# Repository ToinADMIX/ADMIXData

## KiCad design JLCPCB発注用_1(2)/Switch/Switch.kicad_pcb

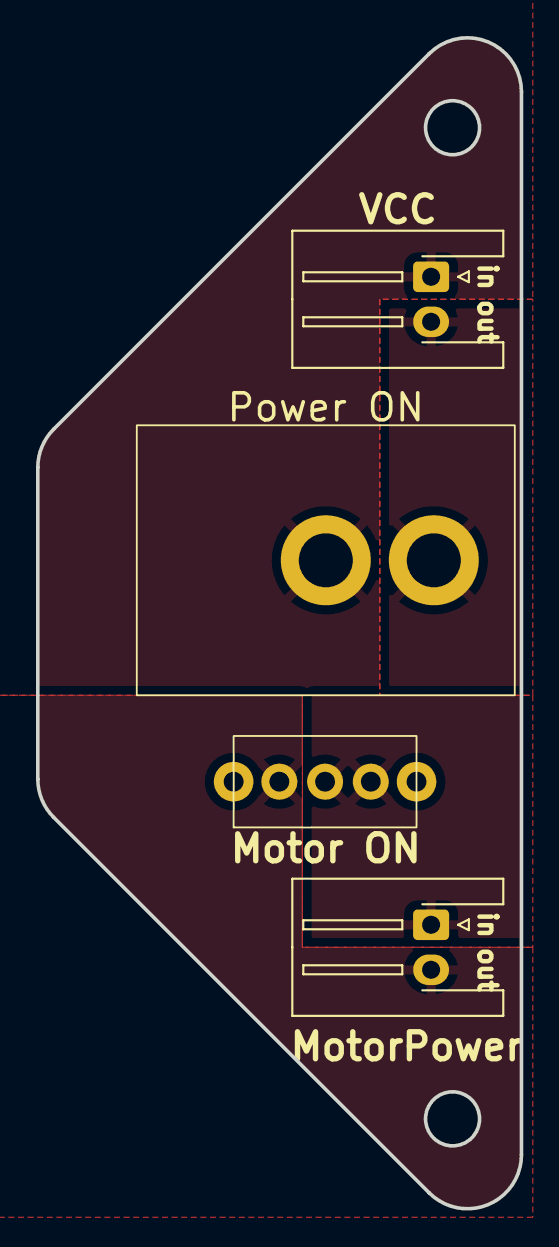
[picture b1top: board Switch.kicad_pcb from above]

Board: 2 copper layers, 26.9 x 65.1 mm, 4 parts (0 on the bottom side), 4 nets, no tracks yet.

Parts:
MotorPower: MotorPower; JST_XH_S2B-XH-A-1_1x02_P2.50mm_Horizontal
Power ON: SW_DPST_x2; DS-850K-S-WD
SW2: SW_DPDT_x2; ToggleSwitch
VCC: VCC; JST_XH_S2B-XH-A-1_1x02_P2.50mm_Horizontal

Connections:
MotorPowerfromPS1: MotorPower.1, SW2.2 (B), SW2.3 (C)
MotorPowertoPS1: MotorPower.2, SW2.1 (A)
VCCfromPS: Power ON.1 (A), VCC.1
VCCtoPS: Power ON.2 (B), VCC.2

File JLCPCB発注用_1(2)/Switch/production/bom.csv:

Designator,Footprint,Quantity,Value,LCSC Part #
MotorPower,JST_XH_S2B-XH-A-1_1x02_P2.50mm_Horizontal,1,MotorPower,
Power ON,DS-850K-S-WD,1,SW_DPST_x2,
SW2,ToggleSwitch,1,SW_DPDT_x2,
VCC,JST_XH_S2B-XH-A-1_1x02_P2.50mm_Horizontal,1,VCC,

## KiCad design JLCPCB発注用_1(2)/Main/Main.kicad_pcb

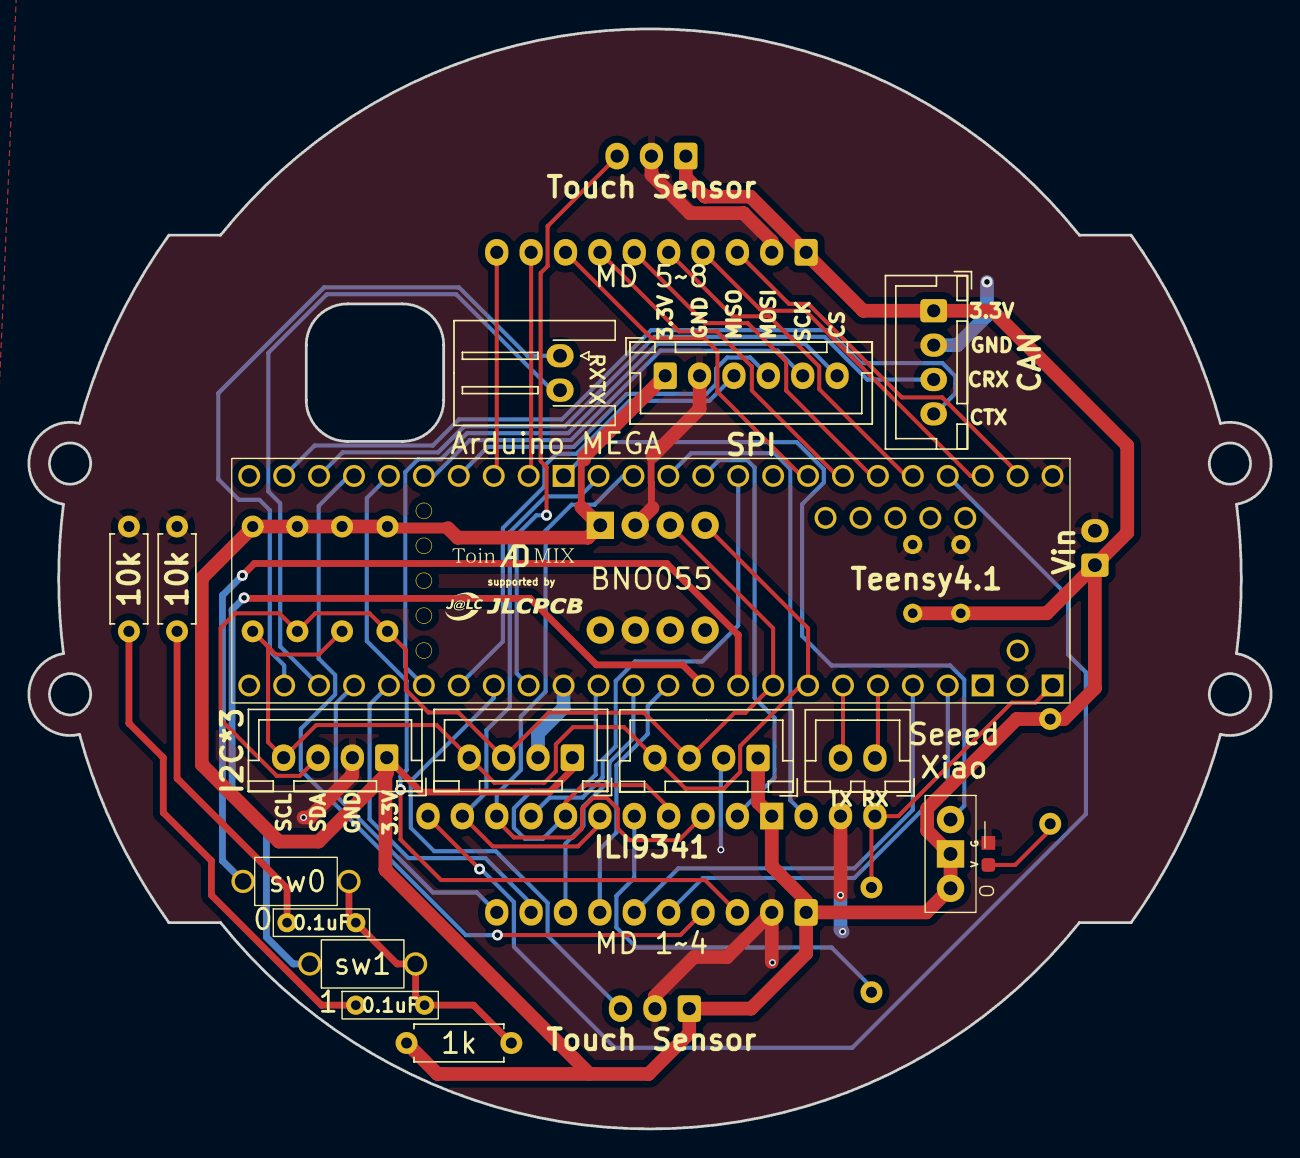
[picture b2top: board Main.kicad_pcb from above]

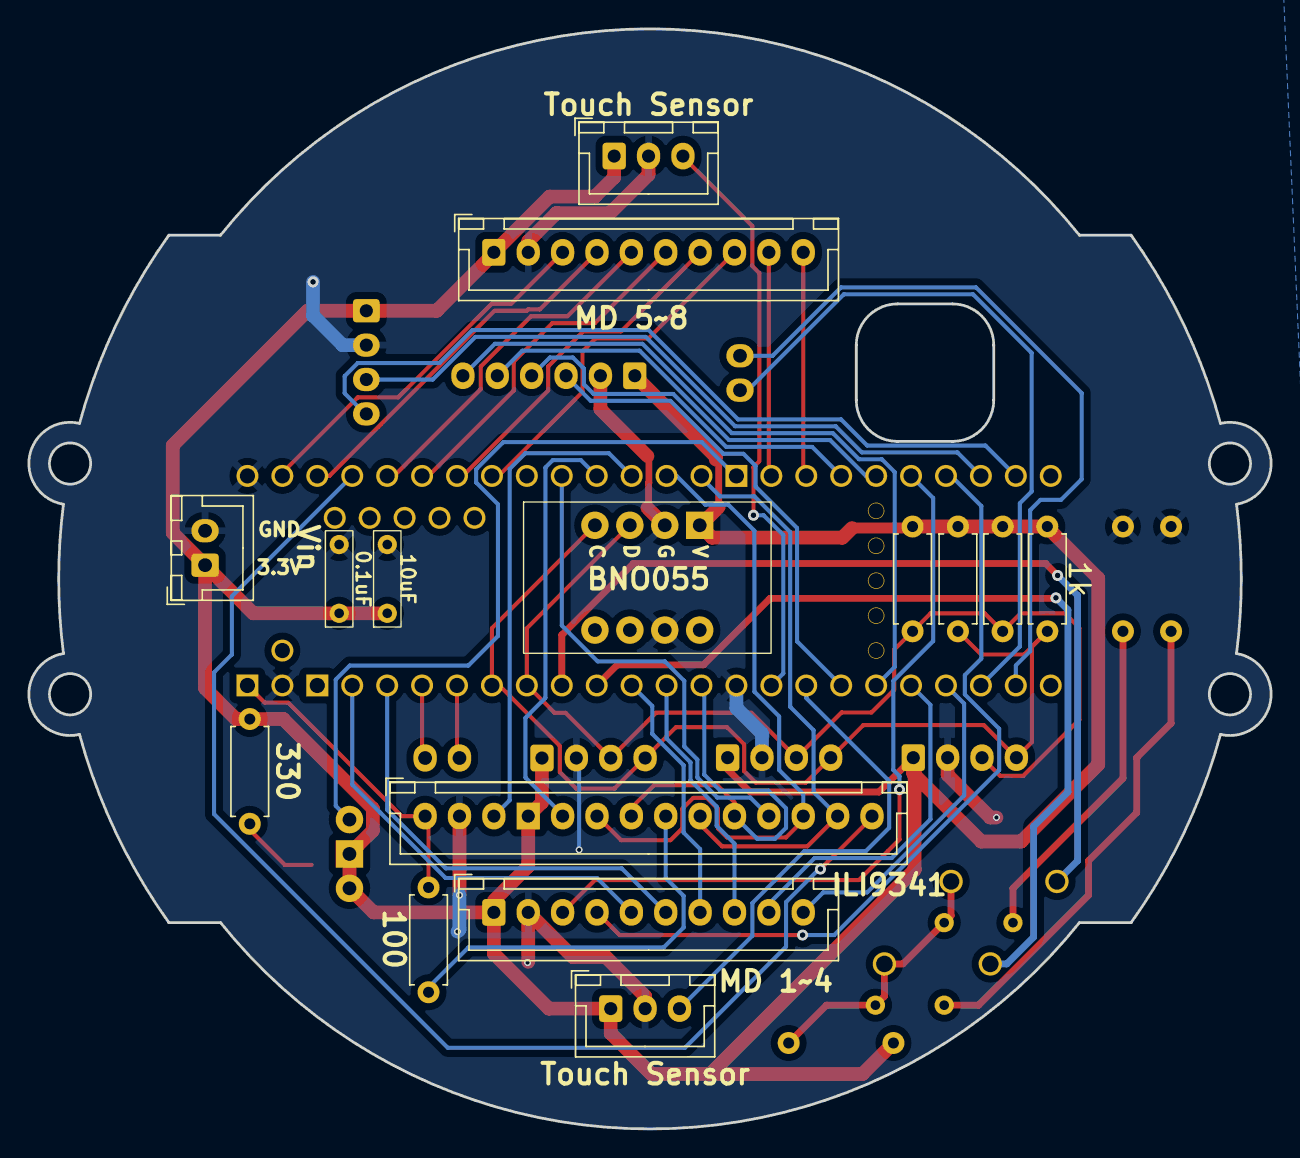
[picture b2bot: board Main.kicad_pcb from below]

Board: 2 copper layers, 90.3 x 80.0 mm, 32 parts (15 on the bottom side), 48 nets.

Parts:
0.1uF, 0.1uF#2: C; Capacitor_0.1uF
0.1uF#3: 0.1uF; Capacitor_0.1uF
1k, 10k, 10k#2: R; R_Axial_DIN0207_L6.3mm_D2.5mm_P7.62mm_Horizontal
1k#2: 2.2k; R_Axial_DIN0207_L6.3mm_D2.5mm_P7.62mm_Horizontal
10uF: 10uF; Capacitor_0.1uF
100: 100; R_Axial_DIN0207_L6.3mm_D2.5mm_P7.62mm_Horizontal
330: 330; R_Axial_DIN0207_L6.3mm_D2.5mm_P7.62mm_Horizontal
BNO055: AE-BNO055-BO
CAN: CAN; JST_XH_B4B-XH-A_1x04_P2.50mm_Vertical
D1: LED_Small; SML-E12P8WT86
I2C*3: Unit V(?); JST_XH_B4B-XH-A_1x04_P2.50mm_Vertical
ILI9341: ILI9341; JST_XH_B14B-XH-A_1x14_P2.50mm_Vertical
J1: Arduino MEGA 2560 PRO MINI; JST_XH_S2B-XH-A-1_1x02_P2.50mm_Horizontal
J3: Seeed Xiao_UI; JST_XH_B2B-XH-A_1x02_P2.50mm_Vertical
J6: HC-SR04; JST_XH_B4B-XH-A_1x04_P2.50mm_Vertical
J9: Pixy 2; JST_XH_B4B-XH-A_1x04_P2.50mm_Vertical
MD 1~4: MotorDriverLeft; JST_XH_B10B-XH-A_1x10_P2.50mm_Vertical
MD 5~8: MotorDriverRight; JST_XH_B10B-XH-A_1x10_P2.50mm_Vertical
R3, R4, R5: 2.2k; R_Axial_DIN0207_L6.3mm_D2.5mm_P7.62mm_Horizontal
SPI: SPI; JST_XH_B6B-XH-A_1x06_P2.50mm_Vertical
SW1: SW_DPDT_x2; SlideSwitch
Teensy4.1: Teensy 4.1
Touch Sensor: Touch SensorBack; JST_XH_B3B-XH-A_1x03_P2.50mm_Vertical
Touch Sensor#2: Touch SensorFront; JST_XH_B3B-XH-A_1x03_P2.50mm_Vertical
Vin: 3.3Vin; JST_XH_B2B-XH-A_1x02_P2.50mm_Vertical
sw0, sw1: SW_Push; TactSwitch_2legs

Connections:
+3.3V: 0.1uF#3.1, 1k.1, 1k#2.1, 10uF.1, 330.1, BNO055.1, CAN.1, I2C*3.1, ILI9341.4, J6.1, J9.1, MD 1~4.1, MD 5~8.1, R3.1, R4.1, R5.1, SPI.1, SW1.2 (B), SW1.3 (C), Touch Sensor.1, Touch Sensor#2.1, Vin.1
Button0: Teensy4.1.17 (SDA1/TX4/A3), sw0.1
Button1: Teensy4.1.16 (SCL/RX4/A2), sw1.1
CRX3ofMain: CAN.3, Teensy4.1.30 (CRX3)
CS1: SPI.6, Teensy4.1.38 (IN1/CS1/A14)
CTX3ofMain: CAN.4, Teensy4.1.31 (CTX3)
Display_CS: ILI9341.3, Teensy4.1.10 (PWM/MQSR/CS)
Display_D/C: ILI9341.5, Teensy4.1.9 (PWM/OUT1C)
Display_LED: 100.2, ILI9341.1, Teensy4.1.102 (Vin(3.6to5.5volts))
Display_SCK: ILI9341.7, ILI9341.10, Teensy4.1.13 (PWM/SCK/(LED))
Display_SDI(MOSI): ILI9341.6, ILI9341.12, Teensy4.1.11 (PWM/CTX1/MOSI)
Display_SDO(MISO): ILI9341.9, ILI9341.13, Teensy4.1.12 (PWM/MQSL/MISO)
Display_T_CS: ILI9341.11, Teensy4.1.8 (PWM/IN1/TX2)
Display_T_IRQ: ILI9341.14, Teensy4.1.2 (PWM/OUT2)
GND: 0.1uF#3.2, 10k.1, 10k#2.1, 10uF.2, BNO055.2, BNO055.7, CAN.2, D1.1 (K), I2C*3.2, ILI9341.2, J6.2, J9.2, MD 1~4.2, MD 5~8.2, SPI.2, Teensy4.1.100 (GND), Teensy4.1.103 (GND), Teensy4.1.105 (GND), Touch Sensor.2, Touch Sensor#2.2, Vin.2
MISO1: SPI.3, Teensy4.1.39 (OUT1A/MISO1/A15)
MOSI1: SPI.4, Teensy4.1.26 (MOSI1/A12)
unnamed: 0.1uF.1, 10k.2
unnamed: 0.1uF.2, 0.1uF#2.2, 1k.2, sw0.2, sw1.2
unnamed: 0.1uF#2.1, 10k#2.2
unnamed: 330.2, D1.2 (A)
unnamed: 100.1, ILI9341.8
unnamed: SW1.1 (A), Teensy4.1.101 (3.3V)
RX5ofMain: J3.1, Teensy4.1.21 (BCLK1/RX5/A7)
RX8ofMain: J1.1, Teensy4.1.34 (RX8)
SCK1: SPI.5, Teensy4.1.27 (SCK1/A13)
SCL: BNO055.4, I2C*3.4, J6.4, J9.4, R3.2, R5.2, Teensy4.1.19 (PWM/SCL/A5)
SDA: 1k#2.2, BNO055.3, I2C*3.3, J6.3, J9.3, R4.2, Teensy4.1.18 (PWM/SDA/A4)
TX5ofMain: J3.2, Teensy4.1.20 (LRCLK1/TX5/A6)
TX8ofMain: J1.2, Teensy4.1.35 (TX8)
TouchSig1: Teensy4.1.41 (A17), Touch Sensor#2.3
TouchSig2: Teensy4.1.40 (A16), Touch Sensor.3
motor1-1: MD 5~8.3, Teensy4.1.0 (PWM/CRX2/CS1/RX1)
motor1-2: MD 5~8.4, Teensy4.1.1 (PWM/CTX2/MISO1/TX1)
motor2-1: MD 5~8.5, Teensy4.1.3 (PWM/LRCLK2)
motor2-2: MD 5~8.6, Teensy4.1.4 (PWM/BCLK2)
motor3-1: MD 5~8.7, Teensy4.1.5 (PWM/IN2)
motor3-2: MD 5~8.8, Teensy4.1.6 (PWM/OUT1D)
motor4-1: MD 5~8.9, Teensy4.1.24 (PWM/SCL2/TX6/A10)
motor4-2: MD 5~8.10, Teensy4.1.25 (PWM/SDA2/RX6/A11)
motor5-1: MD 1~4.3, Teensy4.1.28 (PWM/RX7)
motor5-2: MD 1~4.4, Teensy4.1.29 (PWM/TX7)
motor6-1: MD 1~4.5, Teensy4.1.23 (PWM/MCLK1/CRX1/A9)
motor6-2: MD 1~4.6, Teensy4.1.22 (PWM/CTX1/A8)
motor7-1: MD 1~4.7, Teensy4.1.15 (PWM/S_PDIFIN/RX3/A1)
motor7-2: MD 1~4.8, Teensy4.1.14 (PWM/S_PDIFOUT/TX3/A0)
motor8-1: MD 1~4.9, Teensy4.1.37 (PWM/CS)
motor8-2: MD 1~4.10, Teensy4.1.36 (PWM/CS)

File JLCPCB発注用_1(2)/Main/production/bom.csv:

Designator,Footprint,Quantity,Value,LCSC Part #
"0.1uF_3, 0.1uF_2",Capacitor_0.1uF,2,C,
0.1uF,Capacitor_0.1uF,1,0.1uF,
100,R_Axial_DIN0207_L6.3mm_D2.5mm_P7.62mm_Horizontal,1,100,
"10k_2, 10k, 1k_2",R_Axial_DIN0207_L6.3mm_D2.5mm_P7.62mm_Horizontal,3,R,
10uF,Capacitor_0.1uF,1,10uF,
"1k, R3, R4, R5",R_Axial_DIN0207_L6.3mm_D2.5mm_P7.62mm_Horizontal,4,2.2k,
330,R_Axial_DIN0207_L6.3mm_D2.5mm_P7.62mm_Horizontal,1,330,
BNO055,AE-BNO055-BO,1,AE-BNO055-BO,
CAN,JST_XH_B4B-XH-A_1x04_P2.50mm_Vertical,1,CAN,
D1,SML-E12P8WT86,1,LED_Small,
I2C*3,JST_XH_B4B-XH-A_1x04_P2.50mm_Vertical,1,Unit V(?),
ILI9341,JST_XH_B14B-XH-A_1x14_P2.50mm_Vertical,1,ILI9341,
J1,JST_XH_S2B-XH-A-1_1x02_P2.50mm_Horizontal,1,Arduino MEGA 2560 PRO MINI,
J3,JST_XH_B2B-XH-A_1x02_P2.50mm_Vertical,1,Seeed Xiao_UI,
J6,JST_XH_B4B-XH-A_1x04_P2.50mm_Vertical,1,HC-SR04,
J9,JST_XH_B4B-XH-A_1x04_P2.50mm_Vertical,1,Pixy 2,
MD 1~4,JST_XH_B10B-XH-A_1x10_P2.50mm_Vertical,1,MotorDriverLeft,
MD 5~8,JST_XH_B10B-XH-A_1x10_P2.50mm_Vertical,1,MotorDriverRight,
SPI,JST_XH_B6B-XH-A_1x06_P2.50mm_Vertical,1,SPI,
SW1,SlideSwitch,1,SW_DPDT_x2,
Teensy4.1,Teensy 4.1,1,~,
Touch Sensor_2,JST_XH_B3B-XH-A_1x03_P2.50mm_Vertical,1,Touch SensorBack,
Touch Sensor,JST_XH_B3B-XH-A_1x03_P2.50mm_Vertical,1,Touch SensorFront,
Vin,JST_XH_B2B-XH-A_1x02_P2.50mm_Vertical,1,3.3Vin,
"sw0, sw1",TactSwitch_2legs,2,SW_Push,

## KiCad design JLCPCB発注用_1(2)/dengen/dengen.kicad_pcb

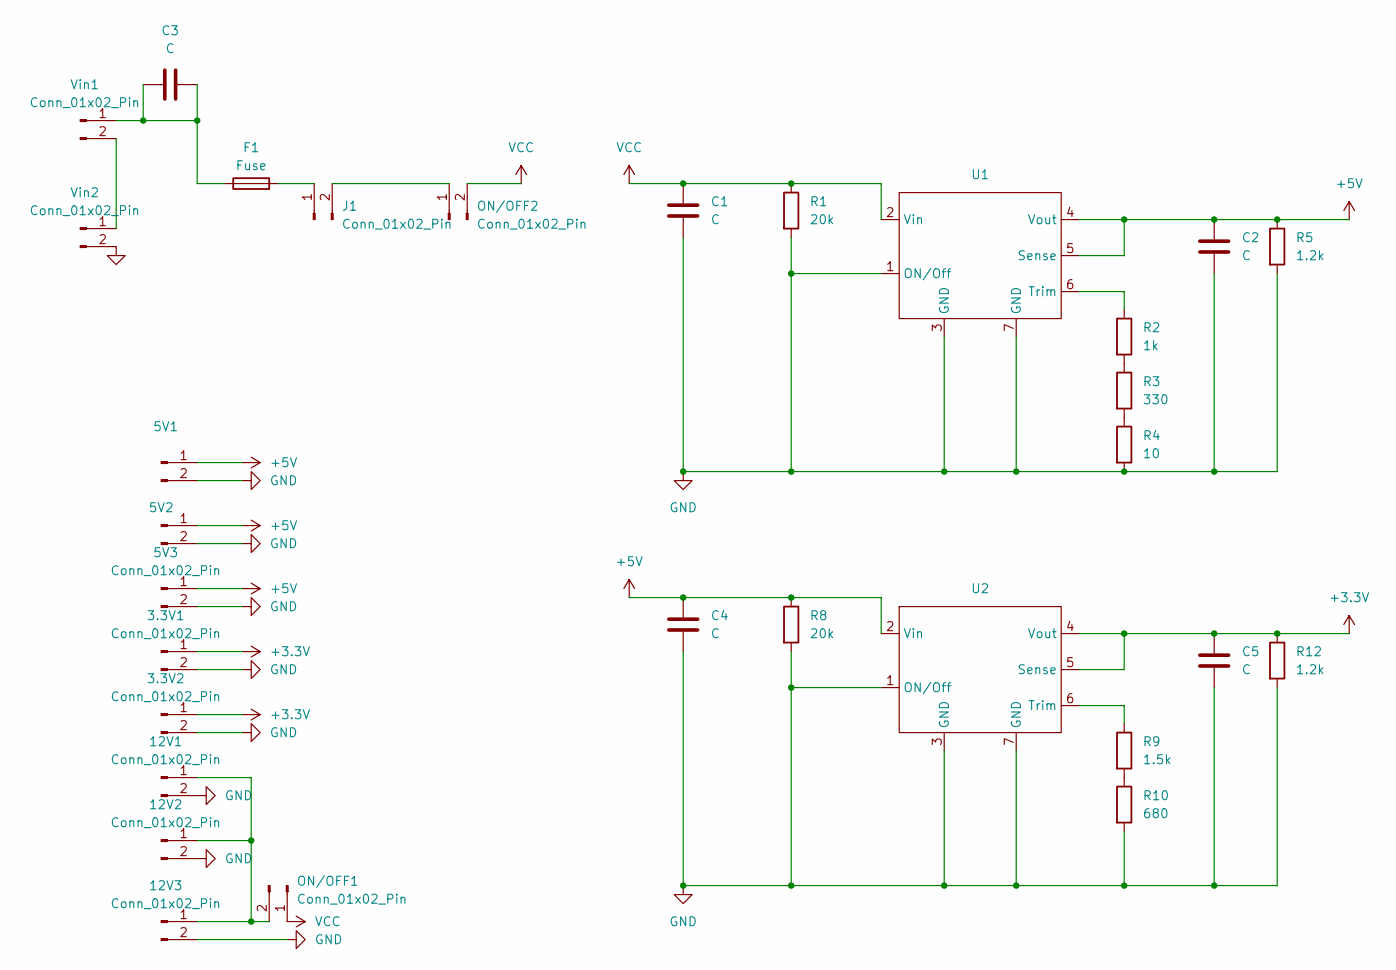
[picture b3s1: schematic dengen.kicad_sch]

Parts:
3.3V1, 3.3V2, 5V1, 5V2, 5V3, 12V1: Conn_01x02_Pin; JST_XH_B2B-XH-A_1x02_P2.50mm_Vertical
12V2, 12V3: Conn_01x02_Pin; JST_XA_S02B-XASK-1N-BN_1x02_P2.50mm_Horizontal
C1, C2, C4, C5: C; C_0805_2012Metric
C3: C; C_Akema
F1: Fuse; fuseclip_Akema
J1: Conn_01x02_Pin; JST_XH_S2B-XH-A-1_1x02_P2.50mm_Horizontal
ON/OFF1, ON/OFF2: Conn_01x02_Pin; JST_XA_S02B-XASK-1N-BN_1x02_P2.50mm_Horizontal
R1, R8: 20k; R_Axial_DIN0207_L6.3mm_D2.5mm_P7.62mm_Horizontal
R2: 1k; R_Axial_DIN0207_L6.3mm_D2.5mm_P7.62mm_Horizontal
R3: 330; R_Axial_DIN0207_L6.3mm_D2.5mm_P7.62mm_Horizontal
R4: 10; R_Axial_DIN0207_L6.3mm_D2.5mm_P7.62mm_Horizontal
R5, R12: 1.2k; R_Axial_DIN0207_L6.3mm_D2.5mm_P7.62mm_Horizontal
R9: 1.5k; R_Axial_DIN0207_L6.3mm_D2.5mm_P7.62mm_Horizontal
R10: 680; R_Axial_DIN0207_L6.3mm_D2.5mm_P7.62mm_Horizontal
U1, U2: dcdc
Vin1, Vin2: Conn_01x02_Pin; JST_XA_S02B-XASK-1N-BN_1x02_P2.50mm_Horizontal

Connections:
+3.3V: 3.3V1.1, 3.3V2.1, C5.1, R12.1, U2.4 (Vout), U2.5 (Sense)
+5V: 5V1.1, 5V2.1, 5V3.1, C2.1, C4.1, R5.1, R8.1, U1.4 (Vout), U1.5 (Sense), U2.2 (Vin)
GND: 3.3V1.2, 3.3V2.2, 5V1.2, 5V2.2, 5V3.2, 12V1.2, 12V2.2, 12V3.2, C1.2, C2.2, C4.2, C5.2, R1.2, R4.2, R5.2, R8.2, R10.2, R12.2, U1.1 (ON/Off), U1.3 (GND), U1.7 (GND), U2.1 (ON/Off), U2.3 (GND), U2.7 (GND), Vin2.2
unnamed: 12V1.1, 12V2.1, 12V3.1, ON/OFF1.2
unnamed: F1.2, J1.1
unnamed 6: J1.2, ON/OFF2.1; also elsewhere on the board
unnamed: R2.2, R3.1
unnamed: R3.2, R4.1
unnamed: R9.2, R10.1
unnamed: R2.1, U1.6 (Trim)
unnamed: R9.1, U2.6 (Trim)
unnamed 12: C3.1, C3.2, F1.1, Vin1.1; also elsewhere on the board
unnamed: Vin1.2, Vin2.1
VCC: C1.1, ON/OFF1.1, ON/OFF2.2, R1.1, U1.2 (Vin)

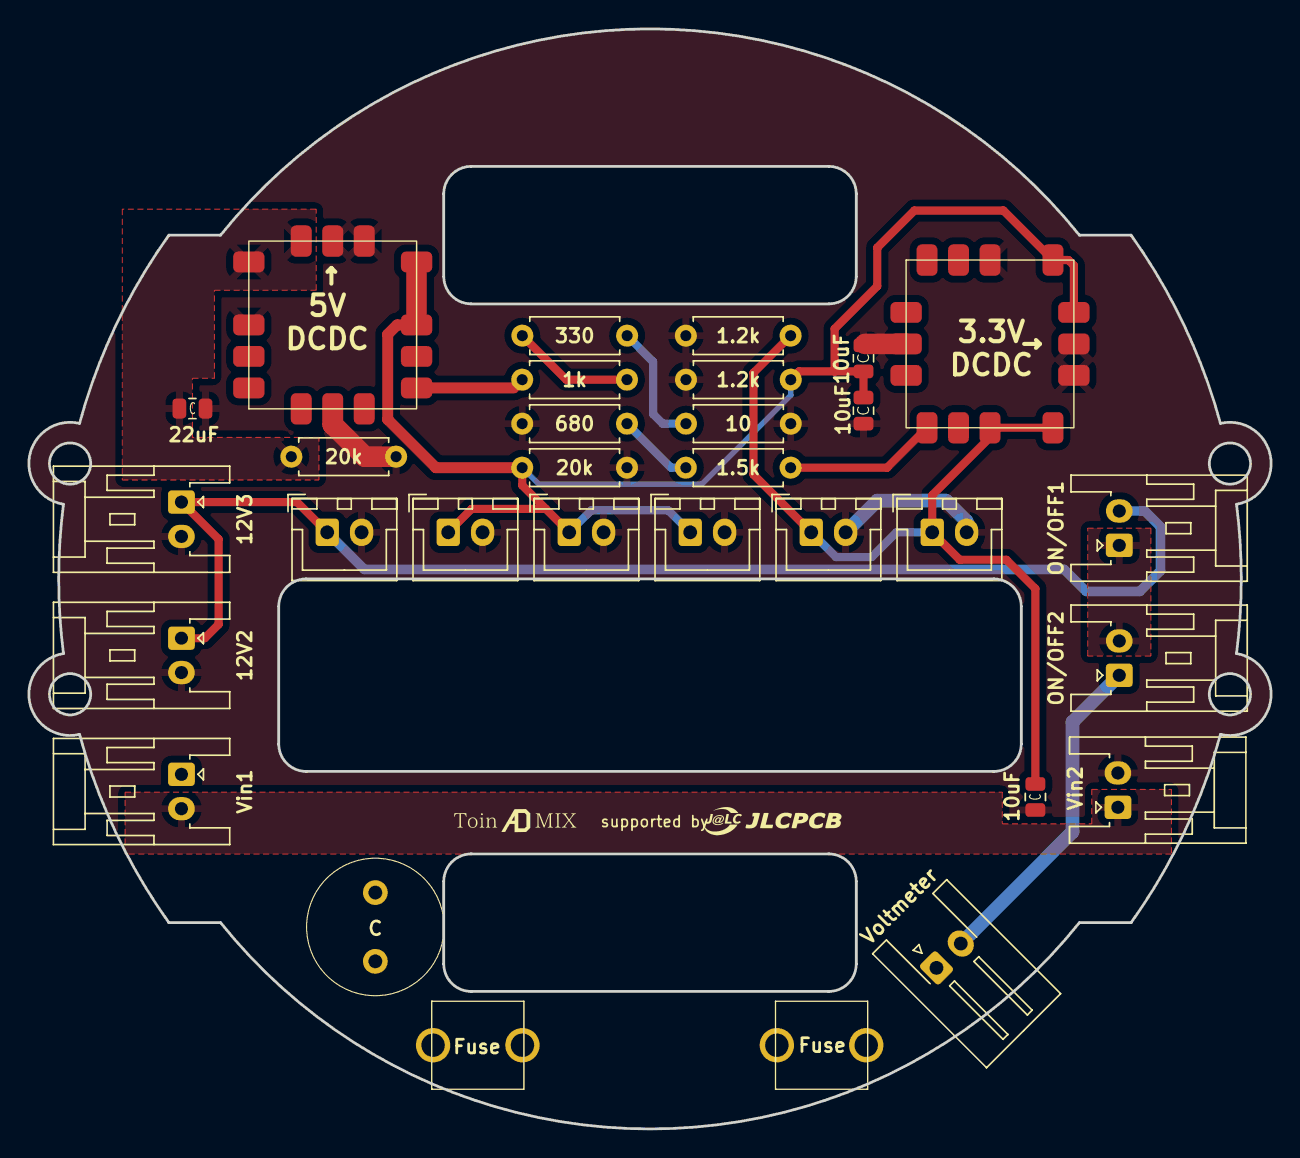
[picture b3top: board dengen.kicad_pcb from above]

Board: 2 copper layers, 90.3 x 80.0 mm, 30 parts (0 on the bottom side), 14 nets.

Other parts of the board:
Fuse: Fuse; fuseclip_Akema
Voltmeter: Conn_01x02_Pin; JST_XH_S2B-XH-A-1_1x02_P2.50mm_Horizontal

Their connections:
unnamed: Fuse.2, Voltmeter.1
unnamed 6: Voltmeter.2; also elsewhere on the board
unnamed 12: Fuse.1; also elsewhere on the board

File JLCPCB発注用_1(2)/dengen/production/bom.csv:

Designator,Footprint,Quantity,Value,LCSC Part #
"12V1, 3.3V1, 3.3V2, 5V1, 5V2, 5V3",JST_XH_B2B-XH-A_1x02_P2.50mm_Vertical,6,Conn_01x02_Pin,
"12V2, 12V3, ON/OFF1, ON/OFF2, Vin1, Vin2",JST_XA_S02B-XASK-1N-BN_1x02_P2.50mm_Horizontal,6,Conn_01x02_Pin,
"C1, C2, C4, C5",0805,4,C,
C3,C_Akema,1,C,
Fuse,fuseclip_Akema,1,Fuse,
"R1, R8",R_Axial_DIN0207_L6.3mm_D2.5mm_P7.62mm_Horizontal,2,20k,
R10,R_Axial_DIN0207_L6.3mm_D2.5mm_P7.62mm_Horizontal,1,680,
"R12, R5",R_Axial_DIN0207_L6.3mm_D2.5mm_P7.62mm_Horizontal,2,1.2k,
R2,R_Axial_DIN0207_L6.3mm_D2.5mm_P7.62mm_Horizontal,1,1k,
R3,R_Axial_DIN0207_L6.3mm_D2.5mm_P7.62mm_Horizontal,1,330,
R4,R_Axial_DIN0207_L6.3mm_D2.5mm_P7.62mm_Horizontal,1,10,
R9,R_Axial_DIN0207_L6.3mm_D2.5mm_P7.62mm_Horizontal,1,1.5k,
"U1, U2",dcdc,2,~,
Voltmeter,JST_XH_S2B-XH-A-1_1x02_P2.50mm_Horizontal,1,Conn_01x02_Pin,

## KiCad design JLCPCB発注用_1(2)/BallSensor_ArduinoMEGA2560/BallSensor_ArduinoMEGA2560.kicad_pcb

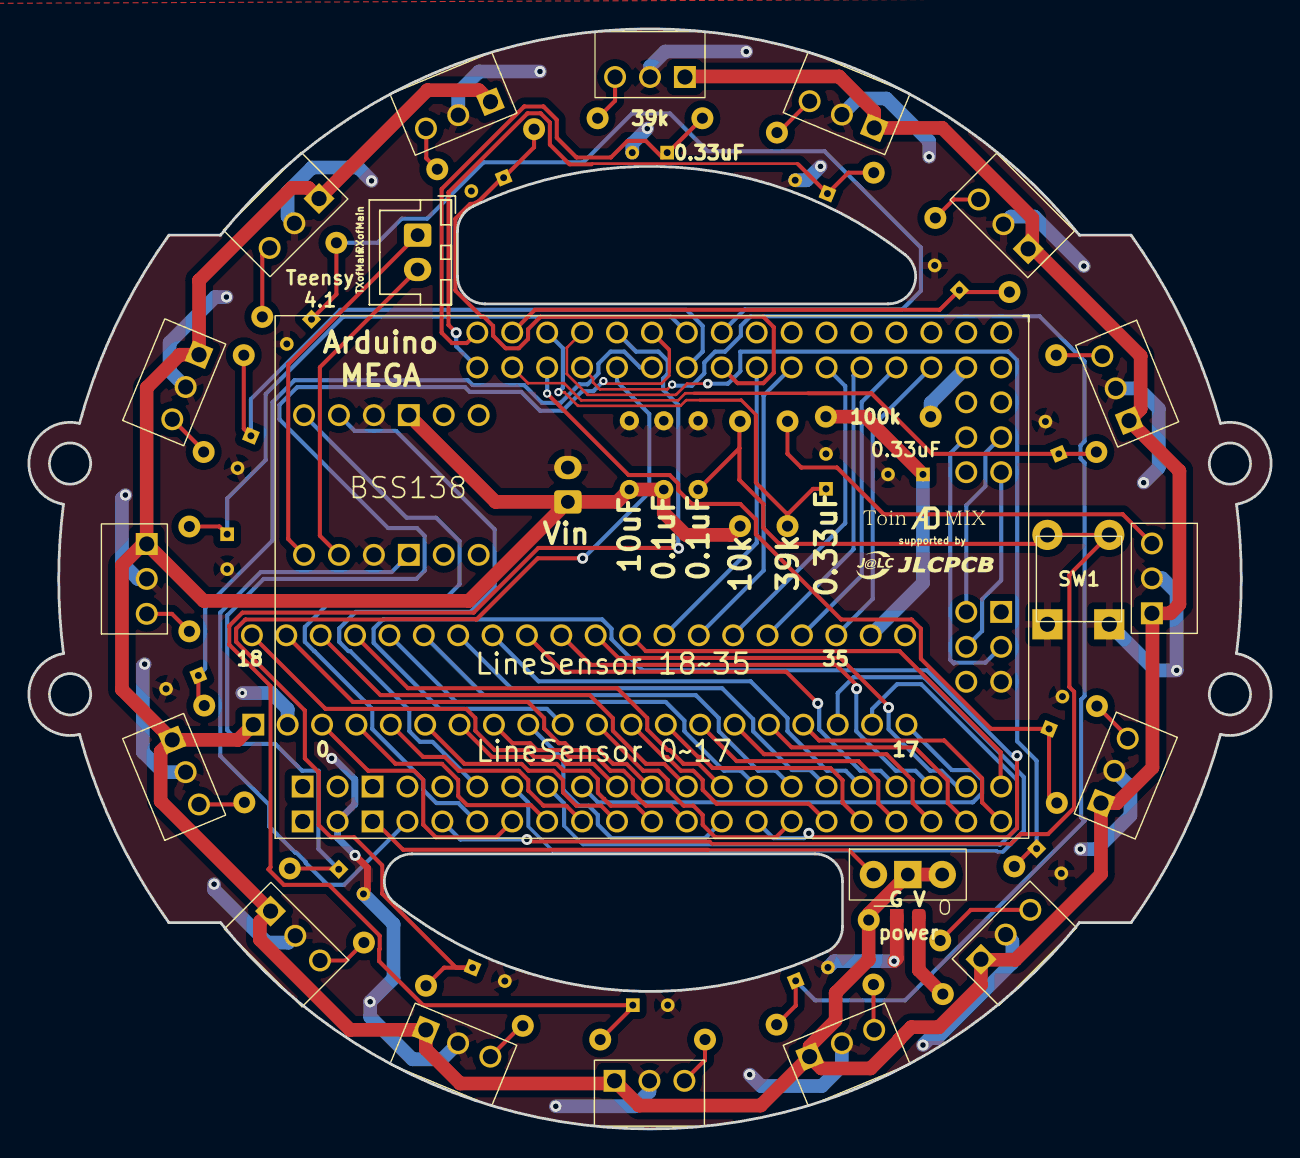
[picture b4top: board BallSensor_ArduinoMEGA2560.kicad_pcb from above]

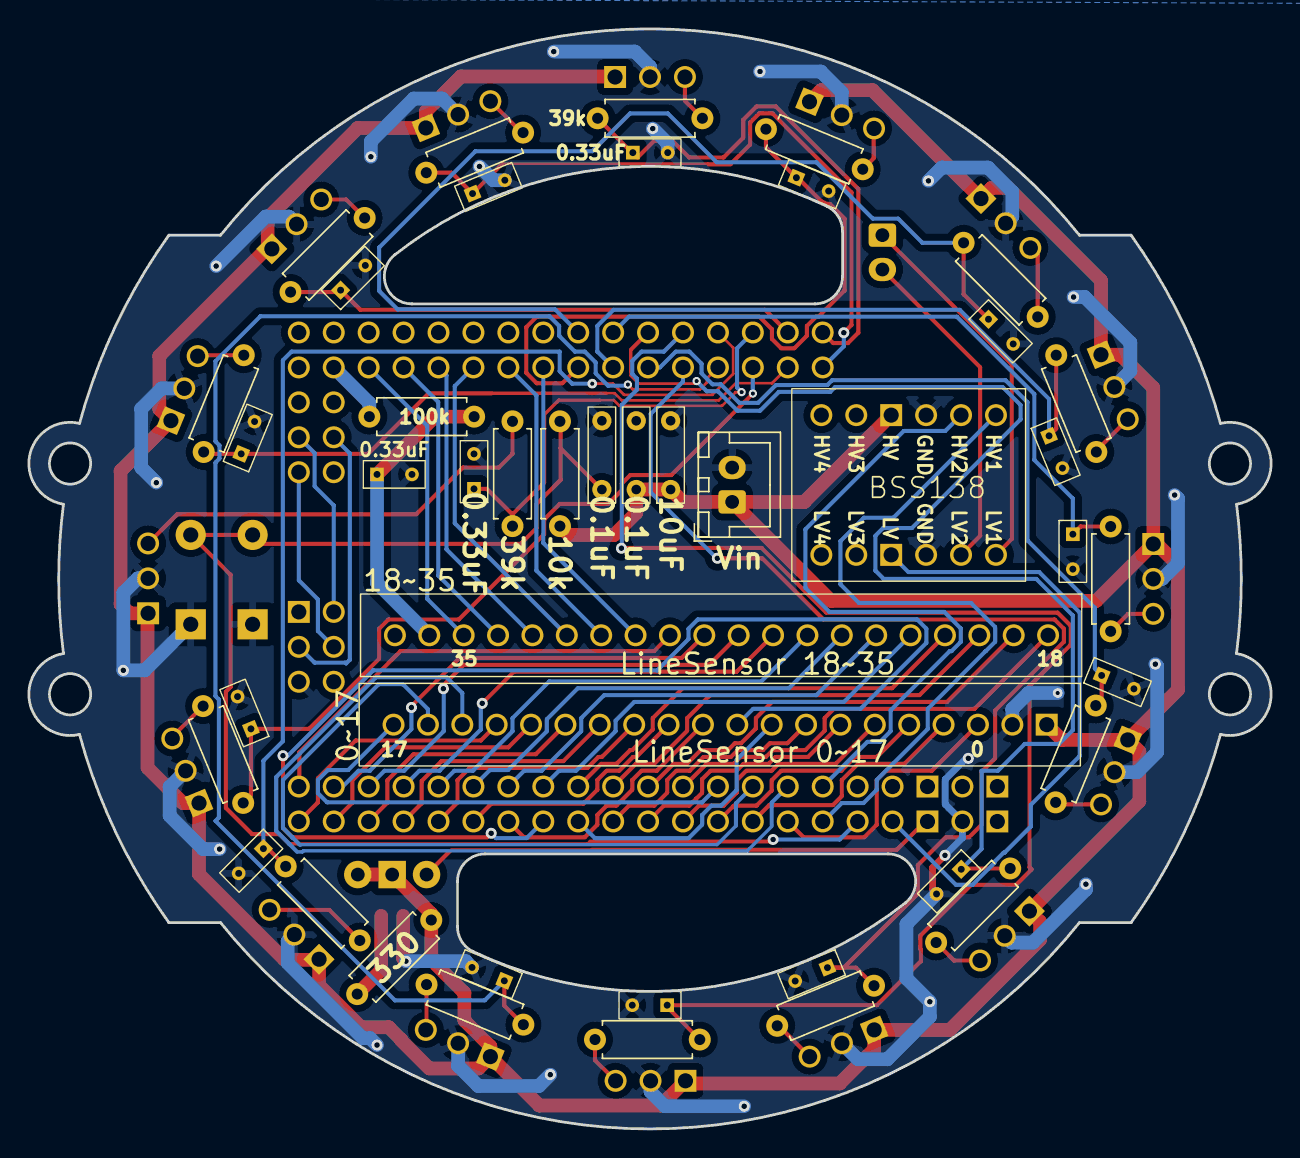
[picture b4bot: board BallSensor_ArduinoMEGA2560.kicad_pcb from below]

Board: 2 copper layers, 90.3 x 80.0 mm, 64 parts (43 on the bottom side), 80 nets.

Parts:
0.1uF, 0.1uF#2: 0.1uF; Capacitor_0.1uF
0.33uF, 0.33uF#2: 0.33uF; Capacitor_0.33uF
10k: 10k; R_Axial_DIN0207_L6.3mm_D2.5mm_P7.62mm_Horizontal
10uF: 10uF; Capacitor_0.1uF
39k: 39k; R_Axial_DIN0207_L6.3mm_D2.5mm_P7.62mm_Horizontal
100k: 100k; R_Axial_DIN0207_L6.3mm_D2.5mm_P7.62mm_Horizontal
BSS138: BSS138
C4, C6, C7, C8, C9, C10, C11, C12, C13, C14, C15, C16, C17, C18, C19: 0.33uF; Capacitor_0.33uF
D2: LED_Small; SML-E12P8WT86
J2: UARTtoMain; JST_XH_B2B-XH-A_1x02_P2.50mm_Vertical
J3: LineSensor0~20; XH Connector 20 pin
J4: LineSensor21~38; XH Connector 21~40 pin
R3, R5, R6, R7, R8, R9, R10, R11, R12, R13, R14, R15, R16, R17, R18: 39k; R_Axial_DIN0207_L6.3mm_D2.5mm_P7.62mm_Horizontal
R4: 330; R_Axial_DIN0207_L6.3mm_D2.5mm_P7.62mm_Horizontal
SW1: SW_Push; Tact Switch
SW2: SW_DPDT_x2; SlideSwitch
U1, U2, U3, U4, U5, U6, U7, U8, U10, U11, U12, U13, U14, U15, U16, U17: TSSP58038_copy
U9: Arduino Mega 2560 Pro Mini
Vin: VCC; JST_XH_B2B-XH-A_1x02_P2.50mm_Vertical

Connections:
+3.3V: BSS138.9 (LV), U9.103 (3V3OUT)
+5V: 0.1uF.1, 10k.1, 10uF.1, BSS138.3 (HV), J3.1, R4.1, SW2.2 (B), SW2.3 (C), U1.3 (Vs), U2.3 (Vs), U3.3 (Vs), U4.3 (Vs), U5.3 (Vs), U6.3 (Vs), U7.3 (Vs), U8.3 (Vs), U10.3 (Vs), U11.3 (Vs), U12.3 (Vs), U13.3 (Vs), U14.3 (Vs), U15.3 (Vs), U16.3 (Vs), U17.3 (Vs), Vin.1
BallSig0: 0.33uF#2.1, 39k.2, U9.97 (PF0/ADC0/54_A0)
BallSig1: C4.1, R3.2, U9.96 (55_A1/ADC1/PF1)
BallSig2: C6.1, R5.2, U9.95 (PF2/ADC2/56_A2)
BallSig3: C7.1, R6.2, U9.94 (57_A3/ADC3/PF3)
BallSig4: C8.1, R7.2, U9.93 (PF4/TCK/ADC4/58_A4)
BallSig5: C9.1, R8.2, U9.92 (59_A5/ADC5/TMS/PF5)
BallSig6: C10.1, R9.2, U9.91 (PF6/TDO/ADC6/60_A6)
BallSig7: C11.1, R10.2, U9.90 (61_A7/ADC7/TDI/PF7)
BallSig8: C12.1, R11.2, U9.89 (PK0/PCINT16/ADC8/62_A8)
BallSig9: C13.1, R12.2, U9.88 (63_A9/ADC9/PCINT17/PK1)
BallSig10: C14.1, R13.2, U9.87 (PK2/PCINT18/ADC10/64_A10)
BallSig11: C15.1, R14.2, U9.86 (65_A11/ADC11/PCINT19/PK3)
BallSig12: C16.1, R15.2, U9.85 (PK4/PCINT20/ADC12/66_A12)
BallSig13: C17.1, R16.2, U9.84 (67_A13/ADC13/PCINT21/PK5)
BallSig14: C18.1, R17.2, U9.83 (PK6/PCINT22/ADC14/68_A14)
BallSig15: C19.1, R18.2, U9.82 (69_A15/ADC15/PCINT23/PK7)
GND: 0.1uF.2, 0.1uF#2.2, 0.33uF.2, 0.33uF#2.2, 10uF.2, BSS138.2 (GND), BSS138.8 (GND), C4.2, C6.2, C7.2, C8.2, C9.2, C10.2, C11.2, C12.2, C13.2, C14.2, C15.2, C16.2, C17.2, C18.2, C19.2, D2.1 (K), J3.2, SW1.1, U1.2 (GND), U2.2 (GND), U3.2 (GND), U4.2 (GND), U5.2 (GND), U6.2 (GND), U7.2 (GND), U8.2 (GND), U9.101 (GND), U9.110 (GND), U10.2 (GND), U11.2 (GND), U12.2 (GND), U13.2 (GND), U14.2 (GND), U15.2 (GND), U16.2 (GND), U17.2 (GND), Vin.2
LineSig0: J3.3, U9.7 (OC3C/INT5/PE5/3)
LineSig1: J3.4, U9.5 (OC3A/AIN1/PE3/5)
LineSig2: J3.5, U9.16 (OC4B/PH4/7)
LineSig3: J3.6, U9.18 (OC2B/PH6/9)
LineSig4: J3.7, U9.24 (OC1A/PCINT5/PB5/11)
LineSig5: J3.8, U9.26 (OC0A/OC1C/PCINT7/PB7/13)
LineSig6: J3.9, U9.63 (RXD3/PCINT9/PJ0/15)
LineSig7: J3.10, U9.12 (RXD2/PH0/17)
LineSig8: J3.11, U9.45 (RXD1/INT2/PD2/19)
LineSig9: J3.12, U9.43 (SCL/INT0/PD0/21)
LineSig10: J3.13, U9.77 (AD1/PA1/23)
LineSig11: J3.14, U9.75 (AD3/PA3/25)
LineSig12: J3.15, U9.73 (AD5/PA5/27)
LineSig13: J3.16, U9.71 (AD7/PA7/29)
LineSig14: J3.17, U9.59 (A14/PC6/31)
LineSig15: J3.18, U9.6 (PE4/INT4/OC3B/2)
LineSig16: J3.19, U9.1 (PG5/OC0B/4)
LineSig17: J3.20, U9.15 (PH3/OC4A/6)
LineSig18: J4.1, U9.17 (PH5/OC4C/8)
LineSig19: J4.2, U9.23 (PB4/PCINT4/OC2A/10)
LineSig20: J4.3, U9.25 (PB6/PCINT6/OC1B/12)
LineSig21: J4.4, U9.64 (PJ1/PCINT10/TXD3/14)
LineSig22: J4.5, U9.13 (PH1/TXD2/16)
LineSig23: J4.6, U9.46 (PD3/INT3/TXD1/18)
LineSig24: J4.7, U9.44 (PD1/INT1/SDA/20)
LineSig25: J4.8, U9.78 (PA0/AD0/22)
LineSig26: J4.9, U9.76 (PA2/AD2/24)
LineSig27: J4.10, U9.74 (PA4/AD4/26)
LineSig28: J4.11, U9.72 (PA6/AD6/28)
LineSig29: J4.12, U9.60 (PC7/A15/30)
LineSig30: J4.13, U9.57 (33/A12/PC4)
LineSig31: J4.14, U9.55 (35/A10/PC2)
LineSig32: J4.15, U9.53 (37/A8/PC0)
LineSig33: J4.16, U9.70 (39/ALE/PG2)
LineSig34: J4.17, U9.51 (41/WR/PG0)
LineSig35: J4.18, U9.41 (43/PL6)
unnamed: D2.2 (A), R4.2
unnamed: SW2.1 (A), U9.102 (5VIN/OUT)
unnamed: 39k.1, U1.1 (OUT)
unnamed: R3.1, U2.1 (OUT)
unnamed: R5.1, U3.1 (OUT)
unnamed: R6.1, U4.1 (OUT)
unnamed: R7.1, U5.1 (OUT)
unnamed: R8.1, U6.1 (OUT)
unnamed: R9.1, U7.1 (OUT)
unnamed: R10.1, U8.1 (OUT)
unnamed: R11.1, U10.1 (OUT)
unnamed: R12.1, U11.1 (OUT)
unnamed: R13.1, U12.1 (OUT)
unnamed: R14.1, U13.1 (OUT)
unnamed: R15.1, U14.1 (OUT)
unnamed: R16.1, U15.1 (OUT)
unnamed: R17.1, U16.1 (OUT)
unnamed: R18.1, U17.1 (OUT)
PWMbeforesmoothing: 100k.1, U9.39 (45/OC5B/PL4)
PWMforComparator: 0.33uF.1, 100k.2, J4.19
RESET: 0.1uF#2.1, 10k.2, SW1.2, U9.104 (RESET)
RXofMain3.3V: BSS138.6 (LV1), J2.1
RXofMain5V: BSS138.0 (HV1), U9.3 (TXD0/PE1/1)
TXofMain3.3V: BSS138.7 (LV2), J2.2
TXofMain5V: BSS138.1 (HV2), U9.2 (PE0/PCINT8/RXD0/0)

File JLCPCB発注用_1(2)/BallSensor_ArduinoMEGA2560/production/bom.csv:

Designator,Footprint,Quantity,Value,LCSC Part #
"0.1uF_2, 0.1uF",Capacitor_0.1uF,2,0.1uF,
"0.33uF_2, 0.33uF, C10, C11, C12, C13, C14, C15, C16, C17, C18, C19, C4, C6, C7, C8, C9",Capacitor_0.33uF,17,0.33uF,
100k,R_Axial_DIN0207_L6.3mm_D2.5mm_P7.62mm_Horizontal,1,100k,
10k,R_Axial_DIN0207_L6.3mm_D2.5mm_P7.62mm_Horizontal,1,10k,
10uF,Capacitor_0.1uF,1,10uF,
"39k, R10, R11, R12, R13, R14, R15, R16, R17, R18, R3, R5, R6, R7, R8, R9",R_Axial_DIN0207_L6.3mm_D2.5mm_P7.62mm_Horizontal,16,39k,
BSS138,BSS138,1,~,
D2,SML-E12P8WT86,1,LED_Small,
J2,JST_XH_B2B-XH-A_1x02_P2.50mm_Vertical,1,UARTtoMain,
J3,XH Connector 20 pin,1,LineSensor0~20,
J4,XH Connector 21~40 pin,1,LineSensor21~38,
R4,R_Axial_DIN0207_L6.3mm_D2.5mm_P7.62mm_Horizontal,1,330,
SW1,Tact Switch,1,SW_Push,
SW2,SlideSwitch,1,SW_DPDT_x2,
"U1, U10, U11, U12, U13, U14, U15, U16, U17, U2, U3, U4, U5, U6, U7, U8",TSSP58038_copy,16,~,
U9,Arduino Mega 2560 Pro Mini,1,~,
Vin,JST_XH_B2B-XH-A_1x02_P2.50mm_Vertical,1,VCC,

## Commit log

2025-06-28 Rename ADMIX_Poster_JapanOpen2025.pdf to ADMIX_Poster_JapanOpen_2025.pdf
2025-06-28 Rename ToinADMIX linesensor center.pdf to LineSensor_1.pdf
